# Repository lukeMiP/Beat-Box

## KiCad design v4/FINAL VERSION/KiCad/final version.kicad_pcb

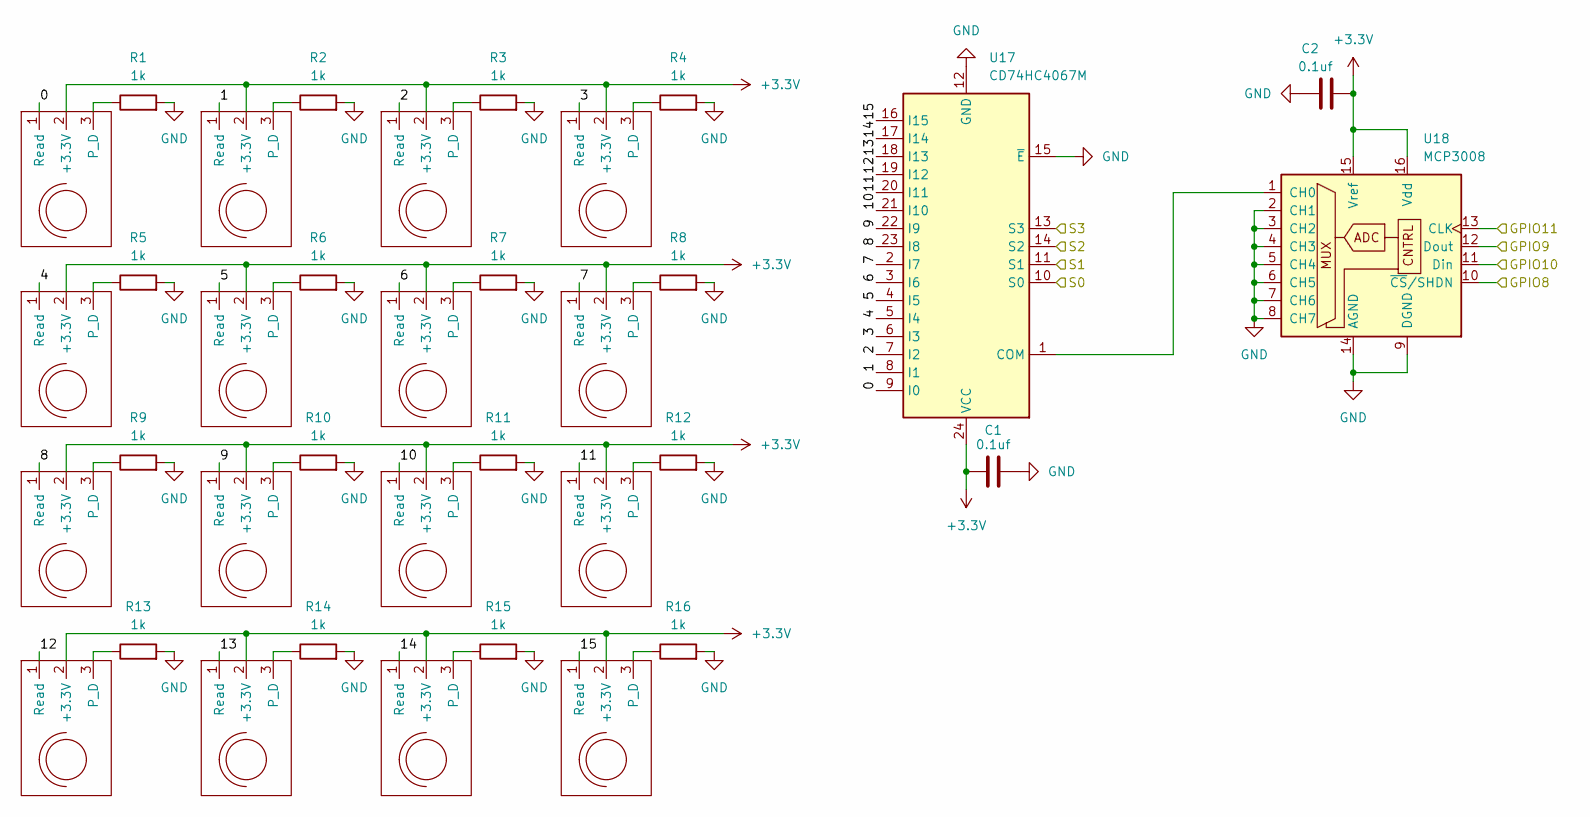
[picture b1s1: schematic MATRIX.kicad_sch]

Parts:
C1, C2: 0.1uf; C_0805_2012Metric_Pad1.18x1.45mm_HandSolder
R1, R2, R3, R4, R5, R6, R7, R8, R9, R10, R11, R12, R13, R14, R15, R16: 1k; R_0805_2012Metric_Pad1.20x1.40mm_HandSolder
U1, U2, U3, U4, U5, U6, U7, U8, U9, U10, U11, U12, U13, U14, U15, U16: VeloPad
U17: CD74HC4067M; SOIC-24W_7.5x15.4mm_P1.27mm
U18: MCP3008; SOIC16-N_MC_MCH-M

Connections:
+3.3V: C1.1, C2.1, U1.2 (+3.3V), U2.2 (+3.3V), U3.2 (+3.3V), U4.2 (+3.3V), U5.2 (+3.3V), U6.2 (+3.3V), U7.2 (+3.3V), U8.2 (+3.3V), U9.2 (+3.3V), U10.2 (+3.3V), U11.2 (+3.3V), U12.2 (+3.3V), U13.2 (+3.3V), U14.2 (+3.3V), U15.2 (+3.3V), U16.2 (+3.3V), U17.24 (VCC), U18.15 (Vref), U18.16 (Vdd); also elsewhere on the board
/MATRIX/0: U1.1 (Read), U17.9 (I0)
/MATRIX/1: U2.1 (Read), U17.8 (I1)
/MATRIX/2: U3.1 (Read), U17.7 (I2)
/MATRIX/3: U4.1 (Read), U17.6 (I3)
/MATRIX/4: U5.1 (Read), U17.5 (I4)
/MATRIX/5: U6.1 (Read), U17.4 (I5)
/MATRIX/6: U7.1 (Read), U17.3 (I6)
/MATRIX/7: U8.1 (Read), U17.2 (I7)
/MATRIX/8: U9.1 (Read), U17.23 (I8)
/MATRIX/9: U10.1 (Read), U17.22 (I9)
/MATRIX/10: U11.1 (Read), U17.21 (I10)
/MATRIX/11: U12.1 (Read), U17.20 (I11)
/MATRIX/12: U13.1 (Read), U17.19 (I12)
/MATRIX/13: U14.1 (Read), U17.18 (I13)
/MATRIX/14: U15.1 (Read), U17.17 (I14)
/MATRIX/15: U16.1 (Read), U17.16 (I15)
/MATRIX/GPIO8: U18.10 (~CS/SHDN); also elsewhere on the board
/MATRIX/GPIO9: U18.12 (Dout); also elsewhere on the board
/MATRIX/GPIO10: U18.11 (Din); also elsewhere on the board
/MATRIX/GPIO11: U18.13 (CLK); also elsewhere on the board
/MATRIX/S0: U17.10 (S0); also elsewhere on the board
/MATRIX/S1: U17.11 (S1); also elsewhere on the board
/MATRIX/S2: U17.14 (S2); also elsewhere on the board
/MATRIX/S3: U17.13 (S3); also elsewhere on the board
GND: C1.2, C2.2, R1.2, R2.2, R3.2, R4.2, R5.2, R6.2, R7.2, R8.2, R9.2, R10.2, R11.2, R12.2, R13.2, R14.2, R15.2, R16.2, U17.12 (GND), U17.15 (~E), U18.2 (CH1), U18.3 (CH2), U18.4 (CH3), U18.5 (CH4), U18.6 (CH5), U18.7 (CH6), U18.8 (CH7), U18.9 (DGND), U18.14 (AGND); also elsewhere on the board
unnamed: R1.1, U1.3 (P_D)
unnamed: R2.1, U2.3 (P_D)
unnamed: R3.1, U3.3 (P_D)
unnamed: R4.1, U4.3 (P_D)
unnamed: R5.1, U5.3 (P_D)
unnamed: R6.1, U6.3 (P_D)
unnamed: R7.1, U7.3 (P_D)
unnamed: R8.1, U8.3 (P_D)
unnamed: R9.1, U9.3 (P_D)
unnamed: R10.1, U10.3 (P_D)
unnamed: R11.1, U11.3 (P_D)
unnamed: R12.1, U12.3 (P_D)
unnamed: R13.1, U13.3 (P_D)
unnamed: R14.1, U14.3 (P_D)
unnamed: R15.1, U15.3 (P_D)
unnamed: R16.1, U16.3 (P_D)
unnamed: U17.1 (COM), U18.1 (CH0)

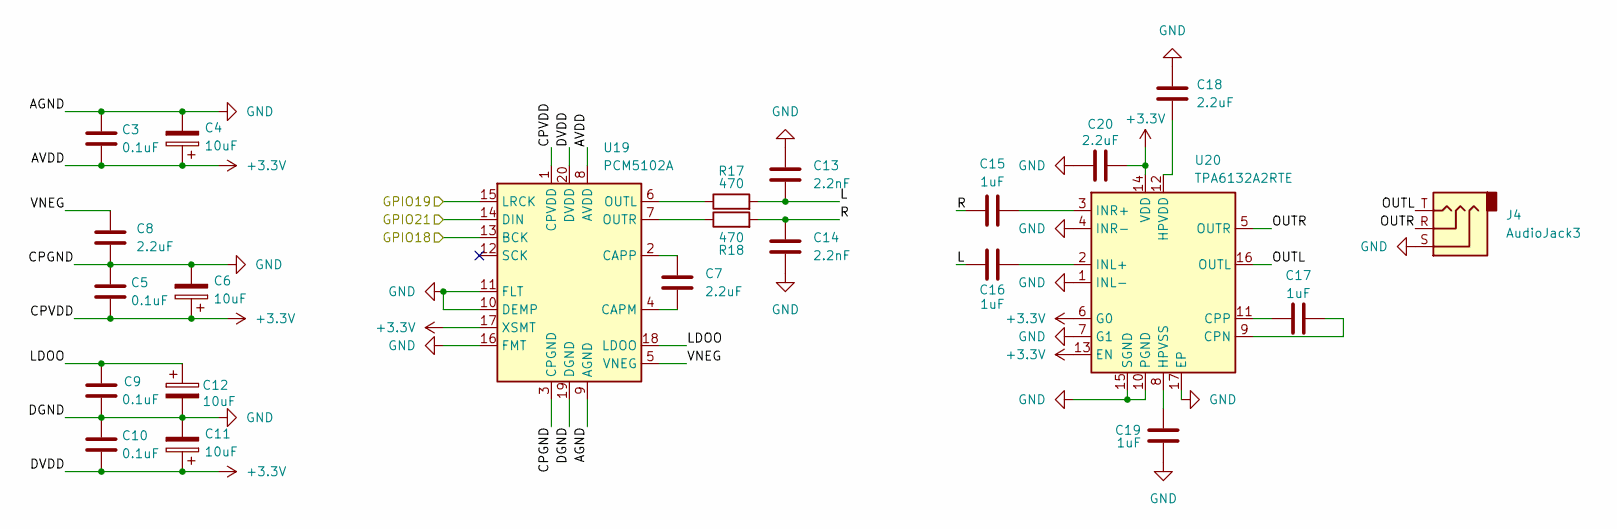
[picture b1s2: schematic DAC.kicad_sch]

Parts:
C3, C5, C9, C10: 0.1uF; C_0805_2012Metric_Pad1.18x1.45mm_HandSolder
C4, C6, C11, C12: 10uF; C_0805_2012Metric_Pad1.18x1.45mm_HandSolder
C7, C8, C18, C20: 2.2uF; C_0805_2012Metric_Pad1.18x1.45mm_HandSolder
C13, C14: 2.2nF; C_0805_2012Metric_Pad1.18x1.45mm_HandSolder
C15, C16, C17, C19: 1uF; C_0805_2012Metric_Pad1.18x1.45mm_HandSolder
J4: AudioJack3; Jack_3.5mm_CUI_SJ-3523-SMT_Horizontal
R17, R18: 470; R_0805_2012Metric_Pad1.20x1.40mm_HandSolder
U19: PCM5102A; TSSOP-20_4.4x6.5mm_P0.65mm
U20: TPA6132A2RTE; WQFN-16-1EP_3x3mm_P0.5mm_EP1.6x1.6mm_ThermalVias

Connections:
+3.3V: C3.2, C4.1, C5.2, C6.1, C10.2, C11.1, C20.2, U19.1 (CPVDD), U19.8 (AVDD), U19.17 (XSMT), U19.20 (DVDD), U20.6 (G0), U20.13 (EN), U20.14 (VDD); also elsewhere on the board
/DAC/GPIO18: U19.13 (BCK); also elsewhere on the board
/DAC/GPIO19: U19.15 (LRCK); also elsewhere on the board
/DAC/GPIO21: U19.14 (DIN); also elsewhere on the board
/DAC/L: C13.2, C16.2, R17.2
/DAC/LDOO: C9.1, C12.1, U19.18 (LDOO)
/DAC/OUTL: J4.T, U20.16 (OUTL)
/DAC/OUTR: J4.R, U20.5 (OUTR)
/DAC/R: C14.1, C15.1, R18.2
/DAC/VNEG: C8.1, U19.5 (VNEG)
GND: C3.1, C4.2, C5.1, C6.2, C8.2, C9.2, C10.1, C11.2, C12.2, C13.1, C14.2, C18.1, C19.1, C20.1, J4.S, U19.3 (CPGND), U19.9 (AGND), U19.10 (DEMP), U19.11 (FLT), U19.16 (FMT), U19.19 (DGND), U20.1 (INL-), U20.4 (INR-), U20.7 (G1), U20.10 (PGND), U20.15 (SGND), U20.17 (EP); also elsewhere on the board
unnamed: C7.2, U19.4 (CAPM)
unnamed: C7.1, U19.2 (CAPP)
unnamed: R17.1, U19.6 (OUTL)
unnamed: R18.1, U19.7 (OUTR)
unnamed: C17.1, U20.9 (CPN)
unnamed: C17.2, U20.11 (CPP)
unnamed: C18.2, U20.12 (HPVDD)
unnamed: C19.2, U20.8 (HPVSS)
unnamed: C16.1, U20.2 (INL+)
unnamed: C15.2, U20.3 (INR+)

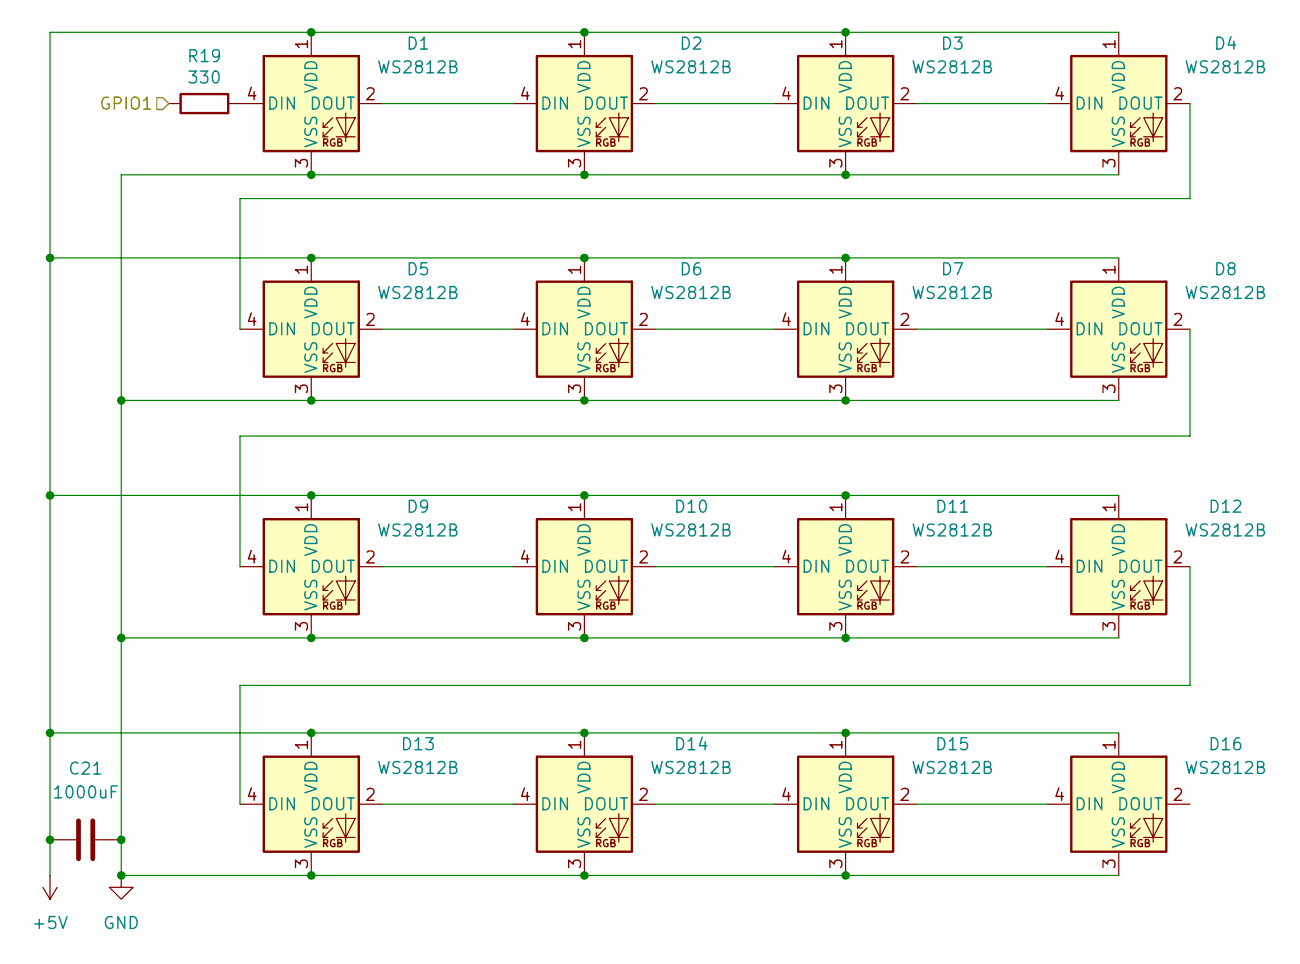
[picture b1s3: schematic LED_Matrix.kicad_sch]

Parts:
C21: 1000uF; C_0805_2012Metric_Pad1.18x1.45mm_HandSolder
D1, D2, D3, D4, D5, D6, D7, D8, D9, D10, D11, D12, D13, D14, D15, D16: WS2812B; LED_WS2812B_PLCC4_5.0x5.0mm_P3.2mm
R19: 330; R_0805_2012Metric_Pad1.20x1.40mm_HandSolder

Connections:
+5V: C21.1, D1.1 (VDD), D2.1 (VDD), D3.1 (VDD), D4.1 (VDD), D5.1 (VDD), D6.1 (VDD), D7.1 (VDD), D8.1 (VDD), D9.1 (VDD), D10.1 (VDD), D11.1 (VDD), D12.1 (VDD), D13.1 (VDD), D14.1 (VDD), D15.1 (VDD), D16.1 (VDD); also elsewhere on the board
/LED_Matrix/GPIO1: R19.1; also elsewhere on the board
GND: C21.2, D1.3 (VSS), D2.3 (VSS), D3.3 (VSS), D4.3 (VSS), D5.3 (VSS), D6.3 (VSS), D7.3 (VSS), D8.3 (VSS), D9.3 (VSS), D10.3 (VSS), D11.3 (VSS), D12.3 (VSS), D13.3 (VSS), D14.3 (VSS), D15.3 (VSS), D16.3 (VSS); also elsewhere on the board
unnamed: D1.4 (DIN), R19.2
unnamed: D1.2 (DOUT), D2.4 (DIN)
unnamed: D2.2 (DOUT), D3.4 (DIN)
unnamed: D3.2 (DOUT), D4.4 (DIN)
unnamed: D4.2 (DOUT), D5.4 (DIN)
unnamed: D5.2 (DOUT), D6.4 (DIN)
unnamed: D6.2 (DOUT), D7.4 (DIN)
unnamed: D7.2 (DOUT), D8.4 (DIN)
unnamed: D8.2 (DOUT), D9.4 (DIN)
unnamed: D9.2 (DOUT), D10.4 (DIN)
unnamed: D10.2 (DOUT), D11.4 (DIN)
unnamed: D11.2 (DOUT), D12.4 (DIN)
unnamed: D12.2 (DOUT), D13.4 (DIN)
unnamed: D13.2 (DOUT), D14.4 (DIN)
unnamed: D14.2 (DOUT), D15.4 (DIN)
unnamed: D15.2 (DOUT), D16.4 (DIN)

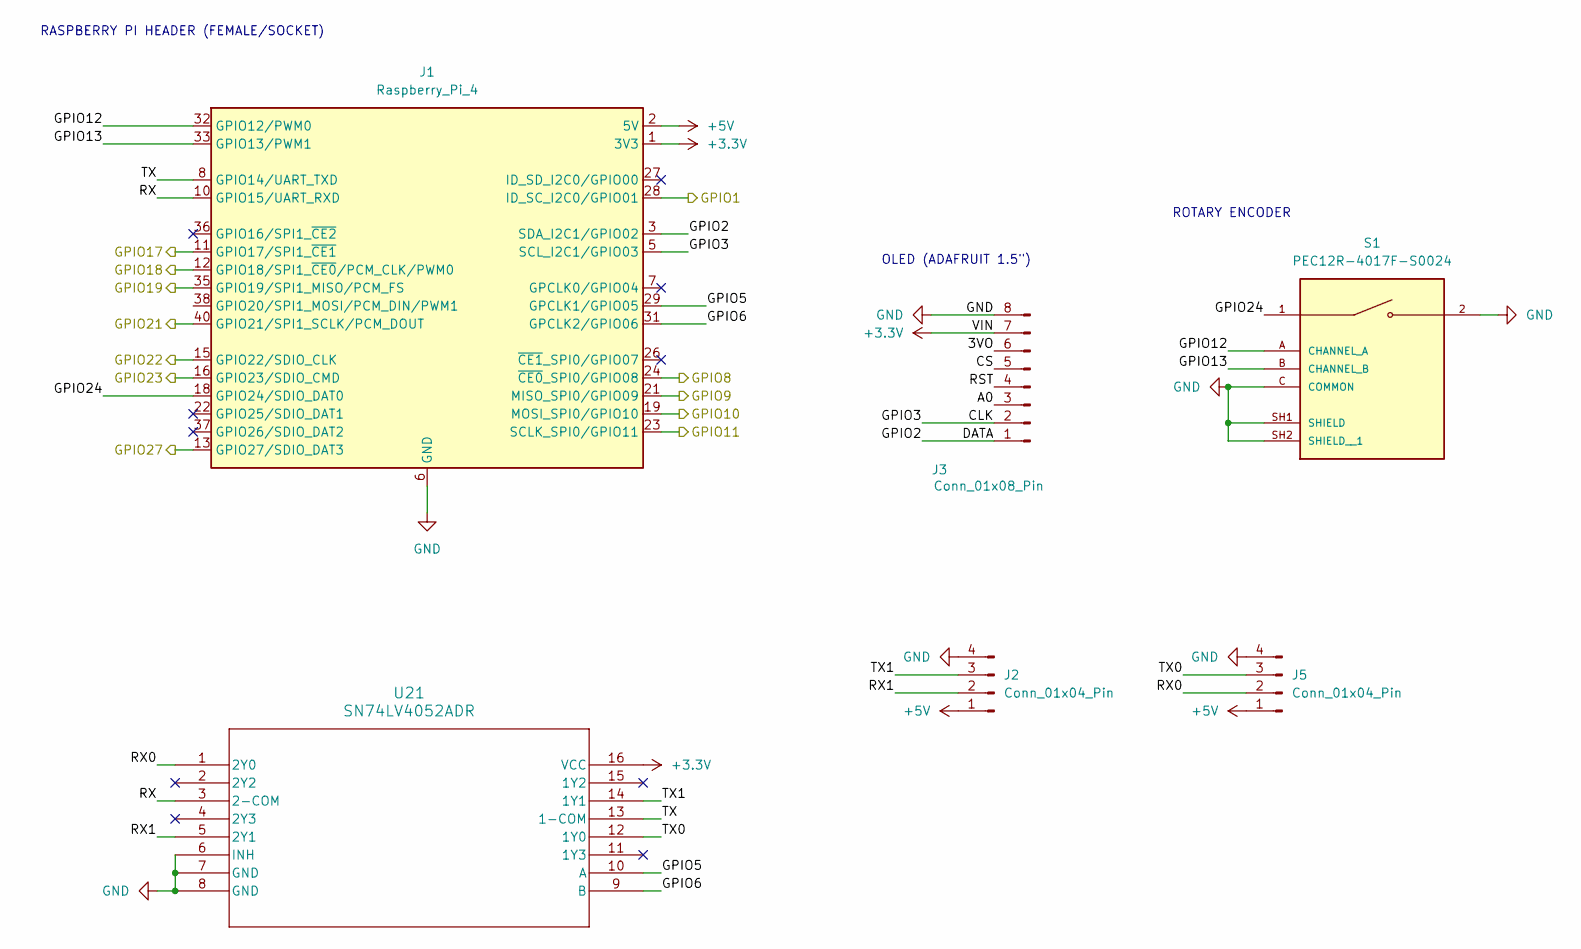
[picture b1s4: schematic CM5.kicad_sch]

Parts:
J1: Raspberry_Pi_4; PinSocket_2x20_P2.54mm_Vertical_SMD
J2, J5: Conn_01x04_Pin; PinHeader_1x04_P2.54mm_Horizontal
J3: Conn_01x08_Pin; PinHeader_1x08_P2.54mm_Vertical
S1: PEC12R-4017F-S0024; XDCR_PEC12R-4017F-S0024; PARTREV 07/21
U21: SN74LV4052ADR; D16

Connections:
+3.3V: J1.1 (3V3), J1.17 (3V3), J3.7, U21.16 (VCC); also elsewhere on the board
+5V: J1.2 (5V), J1.4 (5V), J2.1, J5.1; also elsewhere on the board
/DAC/GPIO18: J1.12 (GPIO18/SPI1_~CE0/PCM_CLK/PWM0); also elsewhere on the board
/DAC/GPIO19: J1.35 (GPIO19/SPI1_MISO/PCM_FS); also elsewhere on the board
/DAC/GPIO21: J1.40 (GPIO21/SPI1_SCLK/PCM_DOUT); also elsewhere on the board
/LED_Matrix/GPIO1: J1.28 (ID_SC_I2C0/GPIO01); also elsewhere on the board
/MATRIX/GPIO8: J1.24 (~CE0_SPI0/GPIO08); also elsewhere on the board
/MATRIX/GPIO9: J1.21 (MISO_SPI0/GPIO09); also elsewhere on the board
/MATRIX/GPIO10: J1.19 (MOSI_SPI0/GPIO10); also elsewhere on the board
/MATRIX/GPIO11: J1.23 (SCLK_SPI0/GPIO11); also elsewhere on the board
/MATRIX/S0: J1.11 (GPIO17/SPI1_~CE1); also elsewhere on the board
/MATRIX/S1: J1.13 (GPIO27/SDIO_DAT3); also elsewhere on the board
/MATRIX/S2: J1.16 (GPIO23/SDIO_CMD); also elsewhere on the board
/MATRIX/S3: J1.15 (GPIO22/SDIO_CLK); also elsewhere on the board
/Rasp Pi/3VO: J3.6
/Rasp Pi/A0: J3.3
/Rasp Pi/CLK: J1.5 (SCL_I2C1/GPIO03), J3.2
/Rasp Pi/CS: J3.5
/Rasp Pi/DATA: J1.3 (SDA_I2C1/GPIO02), J3.1
/Rasp Pi/GPIO5: J1.29 (GPCLK1/GPIO05), U21.10 (A)
/Rasp Pi/GPIO6: J1.31 (GPCLK2/GPIO06), U21.9 (B)
/Rasp Pi/GPIO12: J1.32 (GPIO12/PWM0), S1.A (CHANNEL_A)
/Rasp Pi/GPIO13: J1.33 (GPIO13/PWM1), S1.B (CHANNEL_B)
/Rasp Pi/GPIO24: J1.18 (GPIO24/SDIO_DAT0), S1.1
/Rasp Pi/RST: J3.4
/Rasp Pi/RX: J1.10 (GPIO15/UART_RXD), U21.3 (2-COM)
/Rasp Pi/RX0: J5.2, U21.1 (2Y0)
/Rasp Pi/RX1: J2.2, U21.5 (2Y1)
/Rasp Pi/TX: J1.8 (GPIO14/UART_TXD), U21.13 (1-COM)
/Rasp Pi/TX0: J5.3, U21.12 (1Y0)
/Rasp Pi/TX1: J2.3, U21.14 (1Y1)
GND: J1.6 (GND), J1.9 (GND), J1.14 (GND), J1.20 (GND), J1.25 (GND), J1.30 (GND), J1.34 (GND), J1.39 (GND), J2.4, J3.8, J5.4, S1.2, S1.C (COMMON), S1.SH1 (SHIELD), S1.SH2 (SHIELD__1), U21.6 (INH), U21.7 (GND), U21.8 (GND); also elsewhere on the board

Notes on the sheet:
RASPBERRY PI HEADER (FEMALE/SOCKET)
ROTARY ENCODER
OLED (ADAFRUIT 1.5")

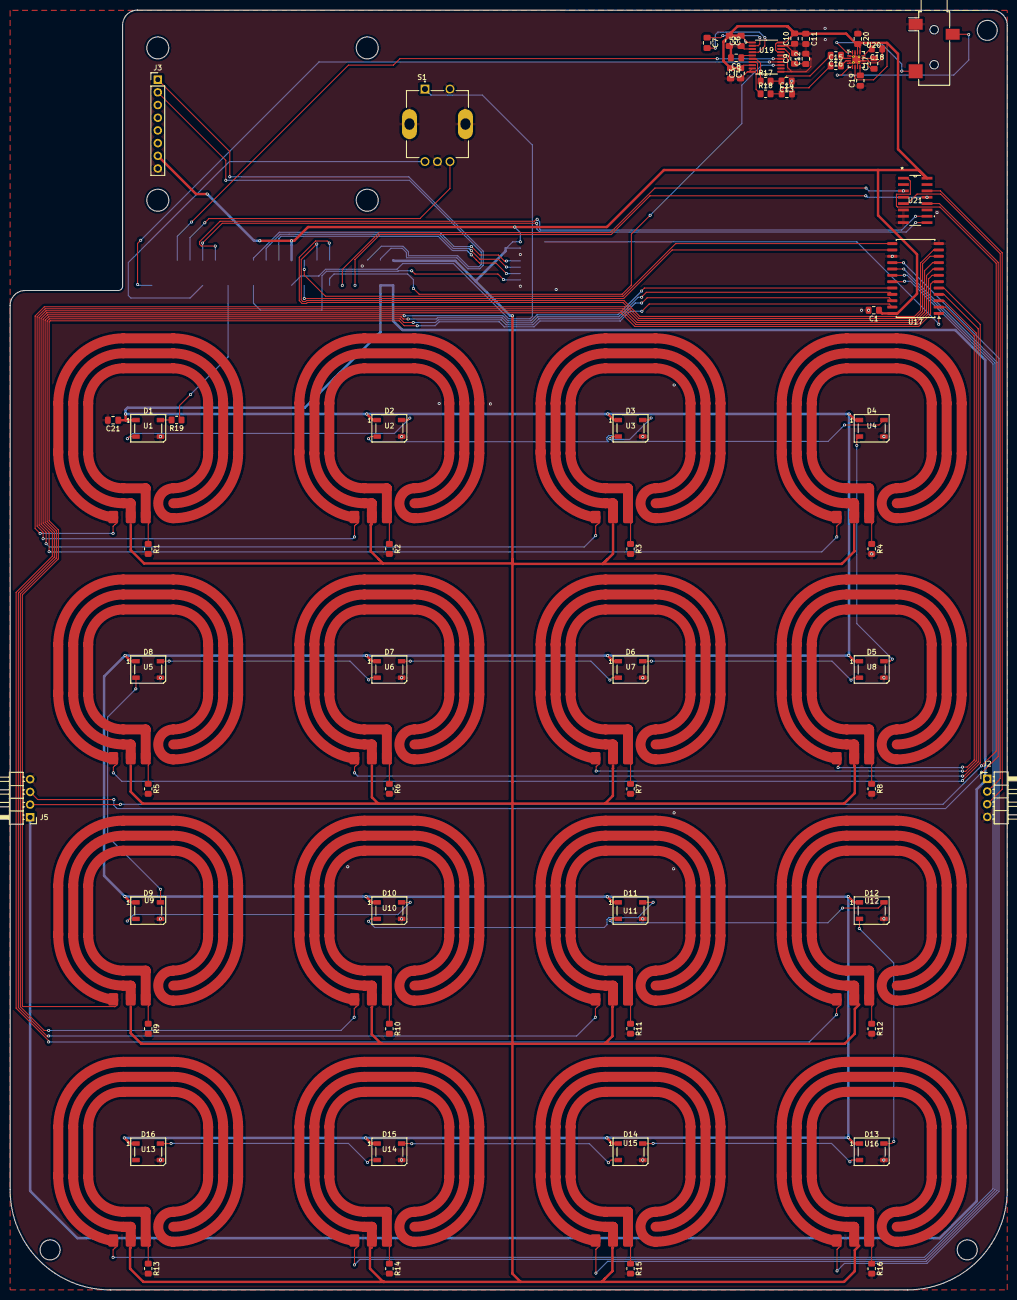
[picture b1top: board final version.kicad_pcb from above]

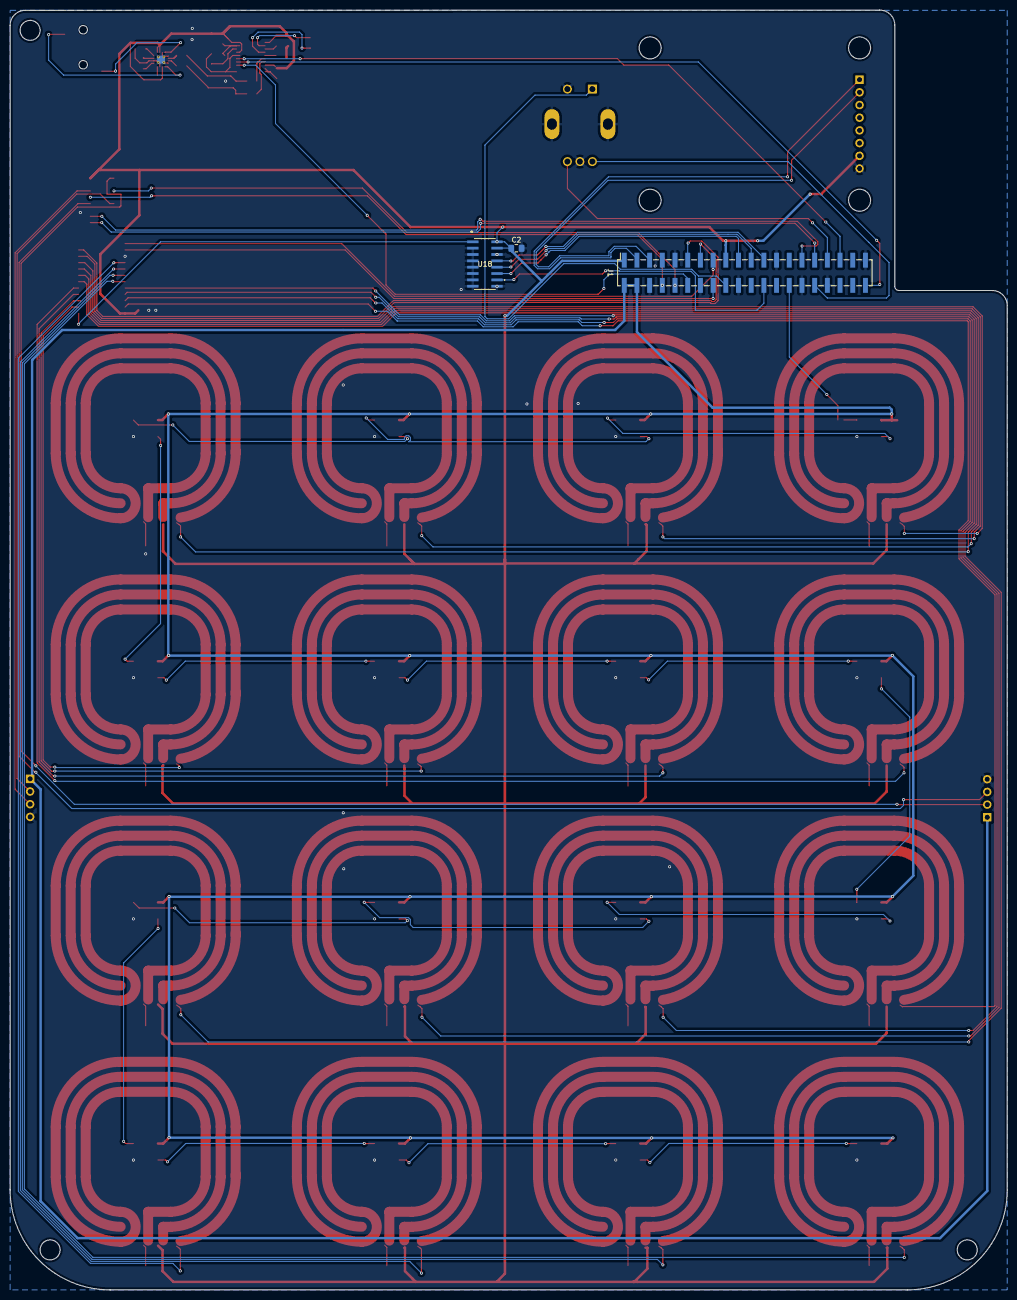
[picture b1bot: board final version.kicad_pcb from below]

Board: 2 copper layers, 199.5 x 256.1 mm, 83 parts (3 on the bottom side), 93 nets.

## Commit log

2025-08-16 update of PCB
2025-08-17 remake
